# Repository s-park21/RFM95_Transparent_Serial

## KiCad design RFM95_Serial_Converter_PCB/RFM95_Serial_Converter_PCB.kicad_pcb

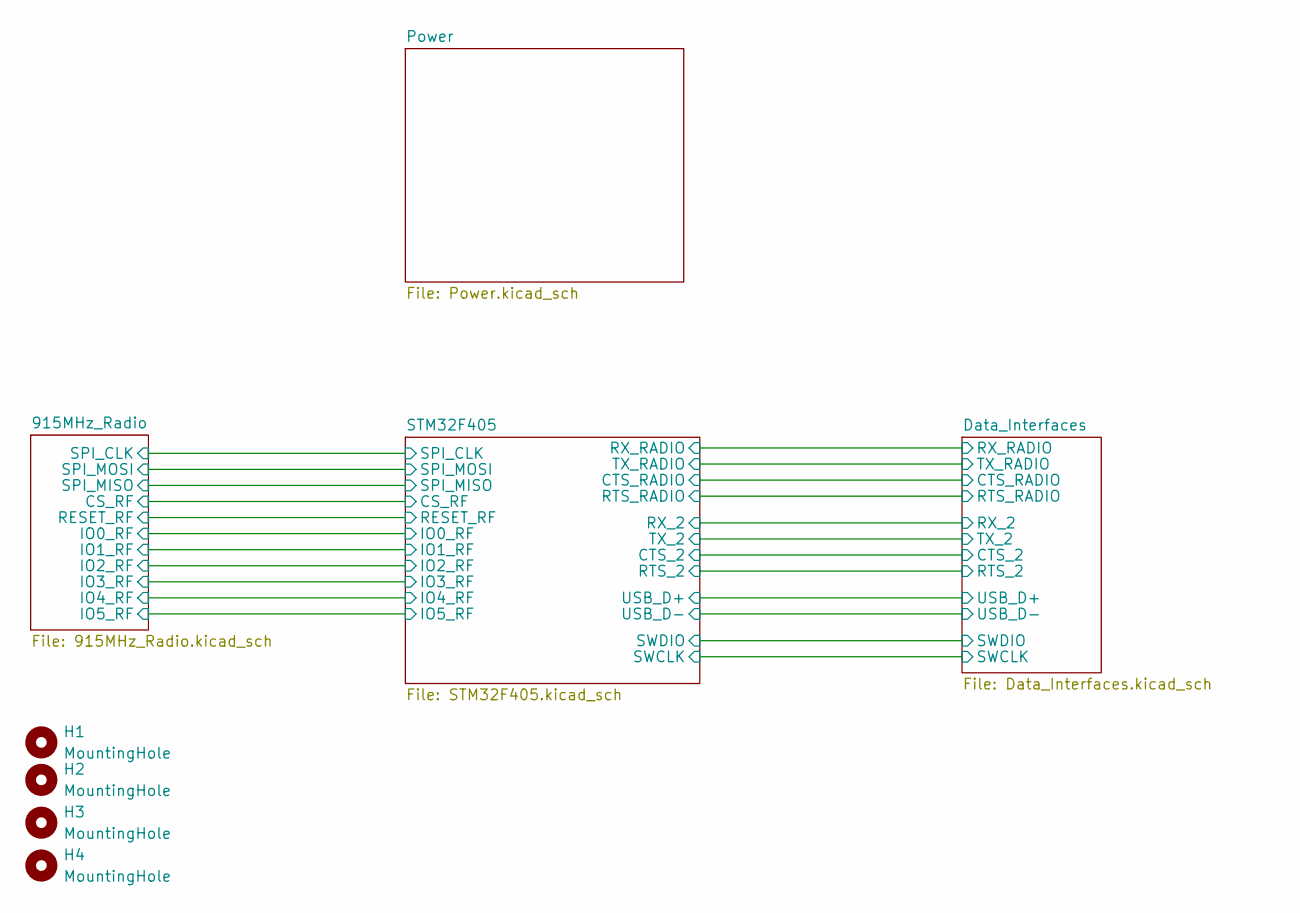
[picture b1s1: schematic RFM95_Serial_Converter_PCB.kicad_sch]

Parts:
H1, H2, H3, H4: MountingHole; MountingHole_2.5mm_Pad

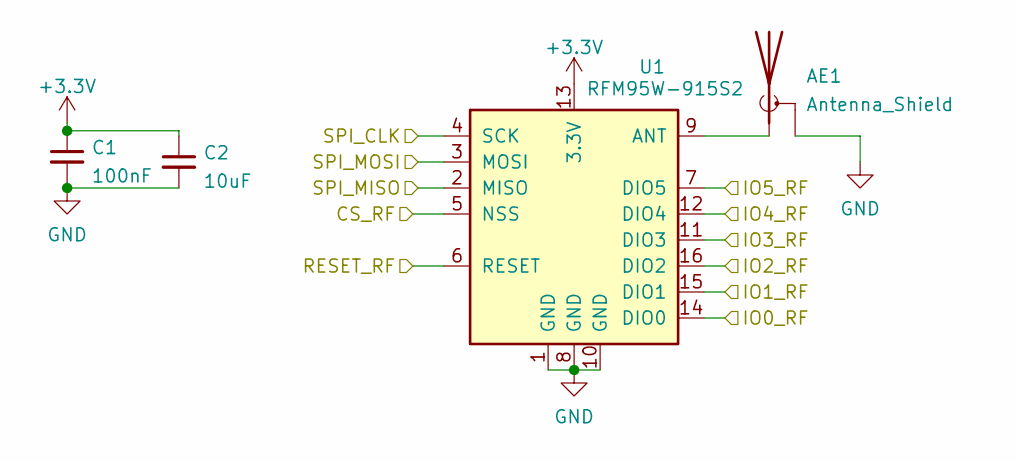
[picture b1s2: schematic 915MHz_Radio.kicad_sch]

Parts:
AE1: Antenna_Shield; SMA_Amphenol_132289_EdgeMount; LCSC C496550
C1: 100nF; C_0603_1608Metric_Pad1.08x0.95mm_HandSolder
C2: 10uF; C_0603_1608Metric_Pad1.08x0.95mm_HandSolder
U1: RFM95W-915S2; HOPERF_RFM9XW_SMD

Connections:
+3V3: C1.1, C2.1, U1.13 (3.3V); also elsewhere on the board
/915MHz_Radio/CS_RF: U1.5 (NSS); also elsewhere on the board
/915MHz_Radio/IO0_RF: U1.14 (DIO0); also elsewhere on the board
/915MHz_Radio/IO1_RF: U1.15 (DIO1); also elsewhere on the board
/915MHz_Radio/IO2_RF: U1.16 (DIO2); also elsewhere on the board
/915MHz_Radio/IO3_RF: U1.11 (DIO3); also elsewhere on the board
/915MHz_Radio/IO4_RF: U1.12 (DIO4); also elsewhere on the board
/915MHz_Radio/IO5_RF: U1.7 (DIO5); also elsewhere on the board
/915MHz_Radio/RESET_RF: U1.6 (RESET); also elsewhere on the board
/915MHz_Radio/SPI_CLK: U1.4 (SCK); also elsewhere on the board
/915MHz_Radio/SPI_MISO: U1.2 (MISO); also elsewhere on the board
/915MHz_Radio/SPI_MOSI: U1.3 (MOSI); also elsewhere on the board
GND: AE1.2 (Shield), C1.2, C2.2, U1.1 (GND), U1.8 (GND), U1.10 (GND); also elsewhere on the board
unnamed: AE1.1 (A), U1.9 (ANT)

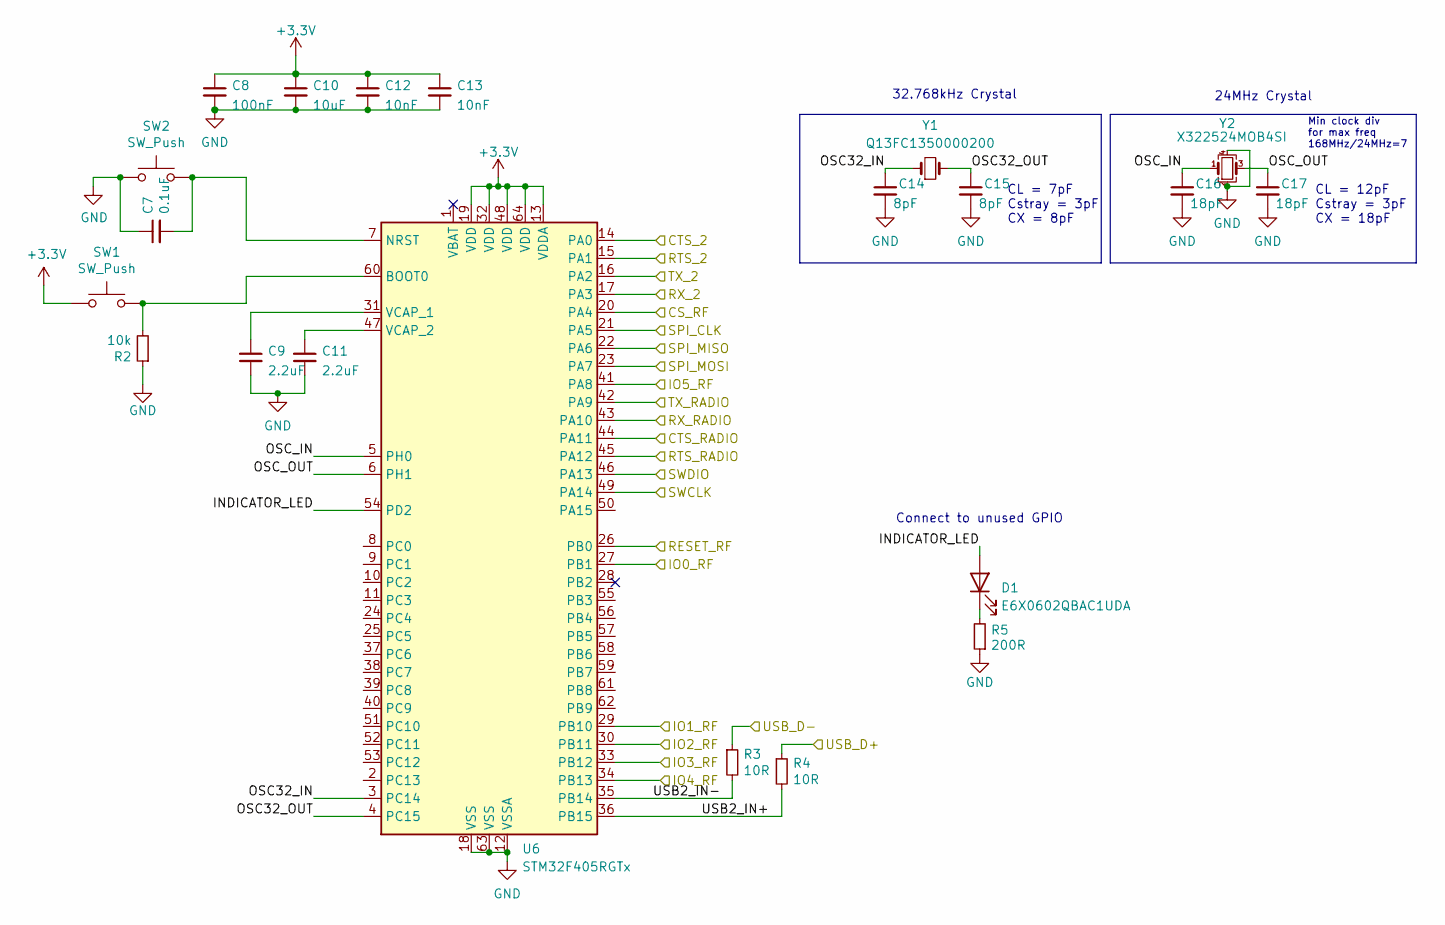
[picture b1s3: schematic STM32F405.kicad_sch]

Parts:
C7: 0.1uF; C_0603_1608Metric_Pad1.08x0.95mm_HandSolder
C8: 100nF; C_0603_1608Metric_Pad1.08x0.95mm_HandSolder
C9, C11: 2.2uF; C_0603_1608Metric_Pad1.08x0.95mm_HandSolder
C10: 10uF; C_0603_1608Metric_Pad1.08x0.95mm_HandSolder
C12, C13: 10nF; C_0603_1608Metric_Pad1.08x0.95mm_HandSolder
C14, C15: 8pF; C_0603_1608Metric_Pad1.08x0.95mm_HandSolder
C16, C17: 18pF; C_0603_1608Metric_Pad1.08x0.95mm_HandSolder
D1: E6X0602QBAC1UDA; LED_0603_1608Metric_Pad1.05x0.95mm_HandSolder; MFR# E6X0602QBAC1UDA; LCSC# C375467
R2: 10k; R_0603_1608Metric_Pad0.98x0.95mm_HandSolder
R3, R4: 10R; R_0603_1608Metric_Pad0.98x0.95mm_HandSolder
R5: 200R; R_0603_1608Metric_Pad0.98x0.95mm_HandSolder
SW1, SW2: SW_Push; SW_Push_1P1T_NO_CK_KSC6xxJ
U6: STM32F405RGTx; LQFP-64_10x10mm_P0.5mm
Y1: Q13FC1350000200; Crystal_SMD_3215-2Pin_3.2x1.5mm; LCSC C48615
Y2: X322524MOB4SI; Crystal_SMD_3225-4Pin_3.2x2.5mm; LCSC C70590

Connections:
+3V3: C8.1, C10.1, C12.1, C13.1, SW1.1, U6.13 (VDDA), U6.19 (VDD), U6.32 (VDD), U6.48 (VDD), U6.64 (VDD); also elsewhere on the board
/915MHz_Radio/CS_RF: U6.20 (PA4); also elsewhere on the board
/915MHz_Radio/IO0_RF: U6.27 (PB1); also elsewhere on the board
/915MHz_Radio/IO1_RF: U6.29 (PB10); also elsewhere on the board
/915MHz_Radio/IO2_RF: U6.30 (PB11); also elsewhere on the board
/915MHz_Radio/IO3_RF: U6.33 (PB12); also elsewhere on the board
/915MHz_Radio/IO4_RF: U6.34 (PB13); also elsewhere on the board
/915MHz_Radio/IO5_RF: U6.41 (PA8); also elsewhere on the board
/915MHz_Radio/RESET_RF: U6.26 (PB0); also elsewhere on the board
/915MHz_Radio/SPI_CLK: U6.21 (PA5); also elsewhere on the board
/915MHz_Radio/SPI_MISO: U6.22 (PA6); also elsewhere on the board
/915MHz_Radio/SPI_MOSI: U6.23 (PA7); also elsewhere on the board
/Data_Interfaces/CTS_2: U6.14 (PA0); also elsewhere on the board
/Data_Interfaces/CTS_RADIO: U6.44 (PA11); also elsewhere on the board
/Data_Interfaces/RTS_2: U6.15 (PA1); also elsewhere on the board
/Data_Interfaces/RTS_RADIO: U6.45 (PA12); also elsewhere on the board
/Data_Interfaces/RX_2: U6.17 (PA3); also elsewhere on the board
/Data_Interfaces/RX_RADIO: U6.43 (PA10); also elsewhere on the board
/Data_Interfaces/SWCLK: U6.49 (PA14); also elsewhere on the board
/Data_Interfaces/SWDIO: U6.46 (PA13); also elsewhere on the board
/Data_Interfaces/TX_2: U6.16 (PA2); also elsewhere on the board
/Data_Interfaces/TX_RADIO: U6.42 (PA9); also elsewhere on the board
/Data_Interfaces/USB_D+: R4.1; also elsewhere on the board
/Data_Interfaces/USB_D-: R3.1; also elsewhere on the board
/STM32F405/INDICATOR_LED: D1.2 (A), U6.54 (PD2)
/STM32F405/OSC32_IN: C14.1, U6.3 (PC14), Y1.1
/STM32F405/OSC32_OUT: C15.1, U6.4 (PC15), Y1.2
/STM32F405/OSC_IN: C16.1, U6.5 (PH0), Y2.1
/STM32F405/OSC_OUT: C17.1, U6.6 (PH1), Y2.3
/STM32F405/USB2_IN+: R4.2, U6.36 (PB15)
/STM32F405/USB2_IN-: R3.2, U6.35 (PB14)
GND: C7.1, C8.2, C9.2, C10.2, C11.2, C12.2, C13.2, C14.2, C15.2, C16.2, C17.2, R2.1, R5.1, SW2.1, U6.12 (VSSA), U6.18 (VSS), U6.63 (VSS), Y2.2, Y2.4; also elsewhere on the board
unnamed: C7.2, SW2.2, U6.7 (NRST)
unnamed: C9.1, U6.31 (VCAP_1)
unnamed: C11.1, U6.47 (VCAP_2)
unnamed: D1.1 (K), R5.2
unnamed: R2.2, SW1.2, U6.60 (BOOT0)

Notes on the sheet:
CL = 7pF Cstray = 3pF CX = 8pF
Connect to unused GPIO
24MHz Crystal
CL = 12pF Cstray = 3pF CX = 18pF
Min clock div for max freq 168MHz/24MHz=7
32.768kHz Crystal

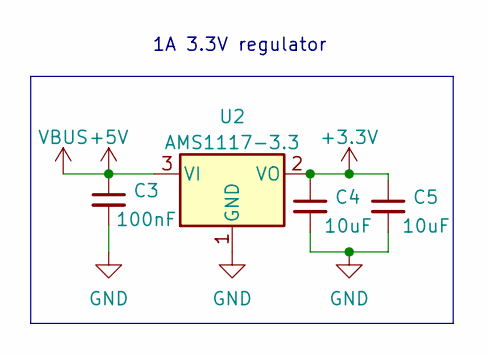
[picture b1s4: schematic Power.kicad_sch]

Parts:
C3: 100nF; C_0603_1608Metric_Pad1.08x0.95mm_HandSolder
C4, C5: 10uF; C_0603_1608Metric_Pad1.08x0.95mm_HandSolder
U2: AMS1117-3.3; SOT-223-3_TabPin2

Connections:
+3V3: C4.1, C5.1, U2.2 (VO); also elsewhere on the board
+5V: C3.1, U2.3 (VI); also elsewhere on the board
GND: C3.2, C4.2, C5.2, U2.1 (GND); also elsewhere on the board

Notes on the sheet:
1A 3.3V regulator

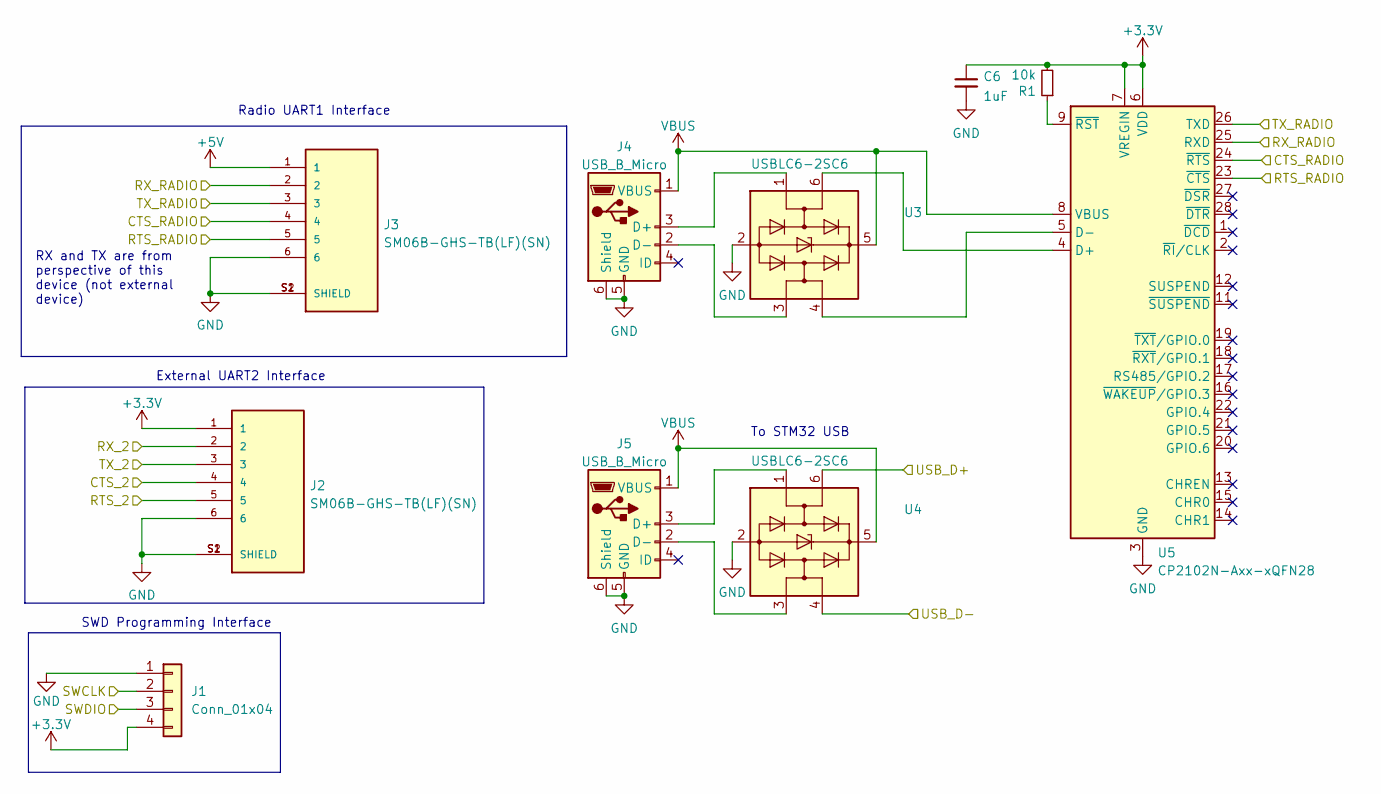
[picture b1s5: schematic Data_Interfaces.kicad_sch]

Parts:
C6: 1uF; C_0603_1608Metric_Pad1.08x0.95mm_HandSolder
J1: Conn_01x04; PinHeader_1x04_P2.54mm_Horizontal
J2, J3: SM06B-GHS-TB(LF)(SN); JST_SM06B-GHS-TB(LF)(SN); PARTREV N/A
J4, J5: USB_B_Micro; USB_Micro-B_Molex-105017-0001
R1: 10k; R_0603_1608Metric_Pad0.98x0.95mm_HandSolder
U3, U4: USBLC6-2SC6; SOT-23-6
U5: CP2102N-Axx-xQFN28; QFN-28-1EP_5x5mm_P0.5mm_EP3.35x3.35mm

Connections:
+3V3: C6.1, J1.4, J2.1, R1.2, U5.6 (VDD), U5.7 (VREGIN); also elsewhere on the board
+5V: J3.1, J4.1 (VBUS), J5.1 (VBUS), U3.5 (VBUS), U4.5 (VBUS), U5.8 (VBUS); also elsewhere on the board
/Data_Interfaces/CTS_2: J2.4; also elsewhere on the board
/Data_Interfaces/CTS_RADIO: J3.4, U5.24 (~RTS); also elsewhere on the board
/Data_Interfaces/RTS_2: J2.5; also elsewhere on the board
/Data_Interfaces/RTS_RADIO: J3.5, U5.23 (~CTS); also elsewhere on the board
/Data_Interfaces/RX_2: J2.2; also elsewhere on the board
/Data_Interfaces/RX_RADIO: J3.2, U5.25 (RXD); also elsewhere on the board
/Data_Interfaces/SWCLK: J1.2; also elsewhere on the board
/Data_Interfaces/SWDIO: J1.3; also elsewhere on the board
/Data_Interfaces/TX_2: J2.3; also elsewhere on the board
/Data_Interfaces/TX_RADIO: J3.3, U5.26 (TXD); also elsewhere on the board
/Data_Interfaces/USB1_D+: J4.3 (D+), U3.1 (I/O1)
/Data_Interfaces/USB1_D-: J4.2 (D-), U3.3 (I/O2)
/Data_Interfaces/USB1_IN_D+: U3.6 (I/O1), U5.4 (D+)
/Data_Interfaces/USB1_IN_D-: U3.4 (I/O2), U5.5 (D-)
/Data_Interfaces/USB2_D+: J5.3 (D+), U4.1 (I/O1)
/Data_Interfaces/USB2_D-: J5.2 (D-), U4.3 (I/O2)
/Data_Interfaces/USB_D+: U4.6 (I/O1); also elsewhere on the board
/Data_Interfaces/USB_D-: U4.4 (I/O2); also elsewhere on the board
GND: C6.2, J1.1, J2.6, J2.S1 (SHIELD), J2.S2 (SHIELD), J3.6, J3.S1 (SHIELD), J3.S2 (SHIELD), J4.5 (GND), J4.6 (Shield), J5.5 (GND), J5.6 (Shield), U3.2 (GND), U4.2 (GND), U5.3 (GND), U5.29 (GND); also elsewhere on the board
unnamed: R1.1, U5.9 (~RST)

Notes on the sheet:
External UART2 Interface
To STM32 USB
RX and TX are from perspective of this device (not external device)
SWD Programming Interface
Radio UART1 Interface

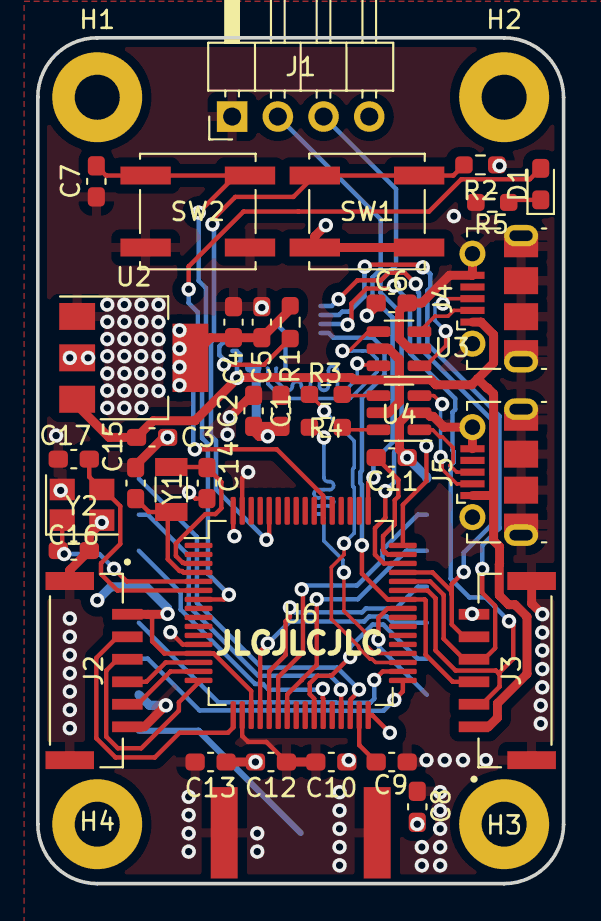
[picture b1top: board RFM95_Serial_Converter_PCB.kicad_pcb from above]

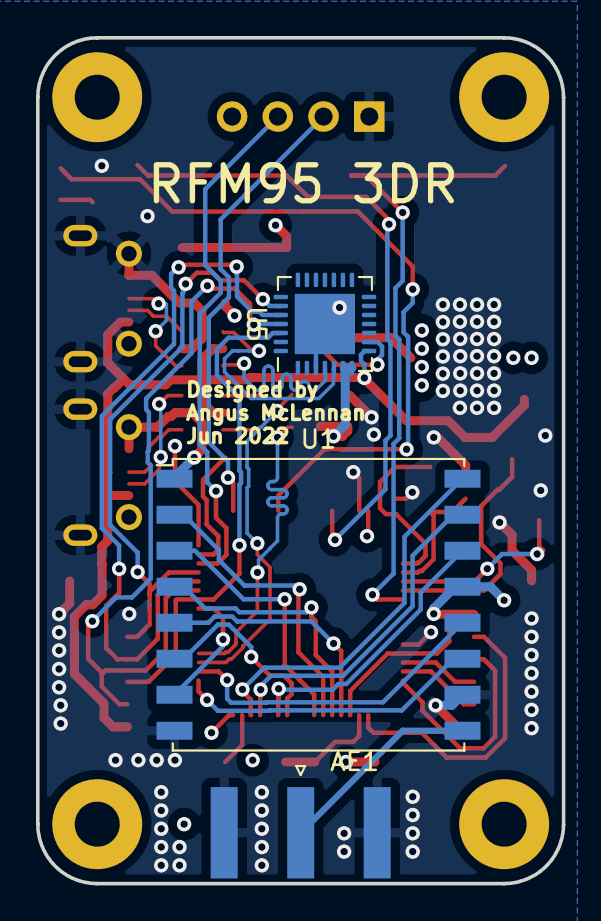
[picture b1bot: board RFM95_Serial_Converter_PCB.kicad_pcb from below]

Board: 4 copper layers, 29.2 x 47.0 mm, 43 parts (3 on the bottom side), 46 nets.

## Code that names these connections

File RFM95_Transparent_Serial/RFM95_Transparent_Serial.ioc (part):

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Mcu.Name=STM32F405RGTx
Mcu.Package=LQFP64
Mcu.UserName=STM32F405RGTx
PA0-WKUP.Mode=CTS_RTS
PA0-WKUP.Signal=USART2_CTS
PA1.Mode=CTS_RTS
PA1.Signal=USART2_RTS
PA10.Mode=Asynchronous
PA10.Signal=USART1_RX
PA11.Signal=USART1_CTS
PA12.Signal=USART1_RTS
PA13.Signal=SYS_JTMS-SWDIO
PA14.Signal=SYS_JTCK-SWCLK
PA2.Mode=Asynchronous
PA2.Signal=USART2_TX
PA3.Mode=Asynchronous
PA3.Signal=USART2_RX
PA4.GPIOParameters=GPIO_Label
PA4.GPIO_Label=RF_SPI_NSS
PA4.Signal=GPIO_Output
PA5.Mode=Full_Duplex_Master
PA5.Signal=SPI1_SCK
PA6.Mode=Full_Duplex_Master
PA6.Signal=SPI1_MISO
PA7.Mode=Full_Duplex_Master
PA7.Signal=SPI1_MOSI
PA8.GPIOParameters=GPIO_Label
PA8.GPIO_Label=IO5_RF
PA8.Signal=GPXTI8
PA9.Mode=Asynchronous
PA9.Signal=USART1_TX
PB0.GPIOParameters=GPIO_Label
PB0.GPIO_Label=RESET_RF
PB0.Signal=GPIO_Output
PB1.GPIOParameters=GPIO_Label
PB1.GPIO_Label=IO0_RF
PB1.Signal=GPXTI1
PB10.GPIOParameters=GPIO_Label
PB10.GPIO_Label=IO1_RF
PB10.Signal=GPXTI10
PB11.GPIOParameters=GPIO_Label
PB11.GPIO_Label=IO2_RF
PB11.Signal=GPXTI11
PB12.GPIOParameters=GPIO_Label
PB12.GPIO_Label=IO3_RF
PB12.Signal=GPXTI12
PB13.GPIOParameters=GPIO_Label
PB13.GPIO_Label=IO4_RF
PB13.Signal=GPXTI13
PB14.Mode=Device_Only_FS
PB14.Signal=USB_OTG_HS_DM
PB15.Mode=Device_Only_FS
PB15.Signal=USB_OTG_HS_DP
PC14-OSC32_IN.Mode=LSE-External-Oscillator
PC14-OSC32_IN.Signal=RCC_OSC32_IN
PC15-OSC32_OUT.Mode=LSE-External-Oscillator
PC15-OSC32_OUT.Signal=RCC_OSC32_OUT
PD2.GPIOParameters=GPIO_Label
PD2.GPIO_Label=INDICATOR_LED
PD2.Signal=GPIO_Output
PH0-OSC_IN.Mode=HSE-External-Oscillator
PH0-OSC_IN.Signal=RCC_OSC_IN
PH1-OSC_OUT.Mode=HSE-External-Oscillator
PH1-OSC_OUT.Signal=RCC_OSC_OUT
RCC.HSE_VALUE=24000000
RCC.SYSCLKFreq_VALUE=168000000
RCC.SYSCLKSource=RCC_SYSCLKSOURCE_PLLCLK
board=custom

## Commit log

2022-06-11 Inital setup
2022-06-11 Swapped to stm32F405
2022-06-11 Schematic almost finished
2022-06-12 Started component placement
2022-06-12 Finalised component placement and board edge
2022-06-15 Routed and ready to order
2022-06-15 Repositioned indicator led and exported step
2022-06-26 Started STM32 cube mx files
2022-06-26 Code finished but untetsted
2022-07-09 Working verison of code
2022-07-11 Working code and PCBs
2022-07-16 Single way comms works. Data rate slow
2022-07-22 RFM95 register setting
2022-07-23 Added FSK payload length function
2022-08-02 Working DMA
